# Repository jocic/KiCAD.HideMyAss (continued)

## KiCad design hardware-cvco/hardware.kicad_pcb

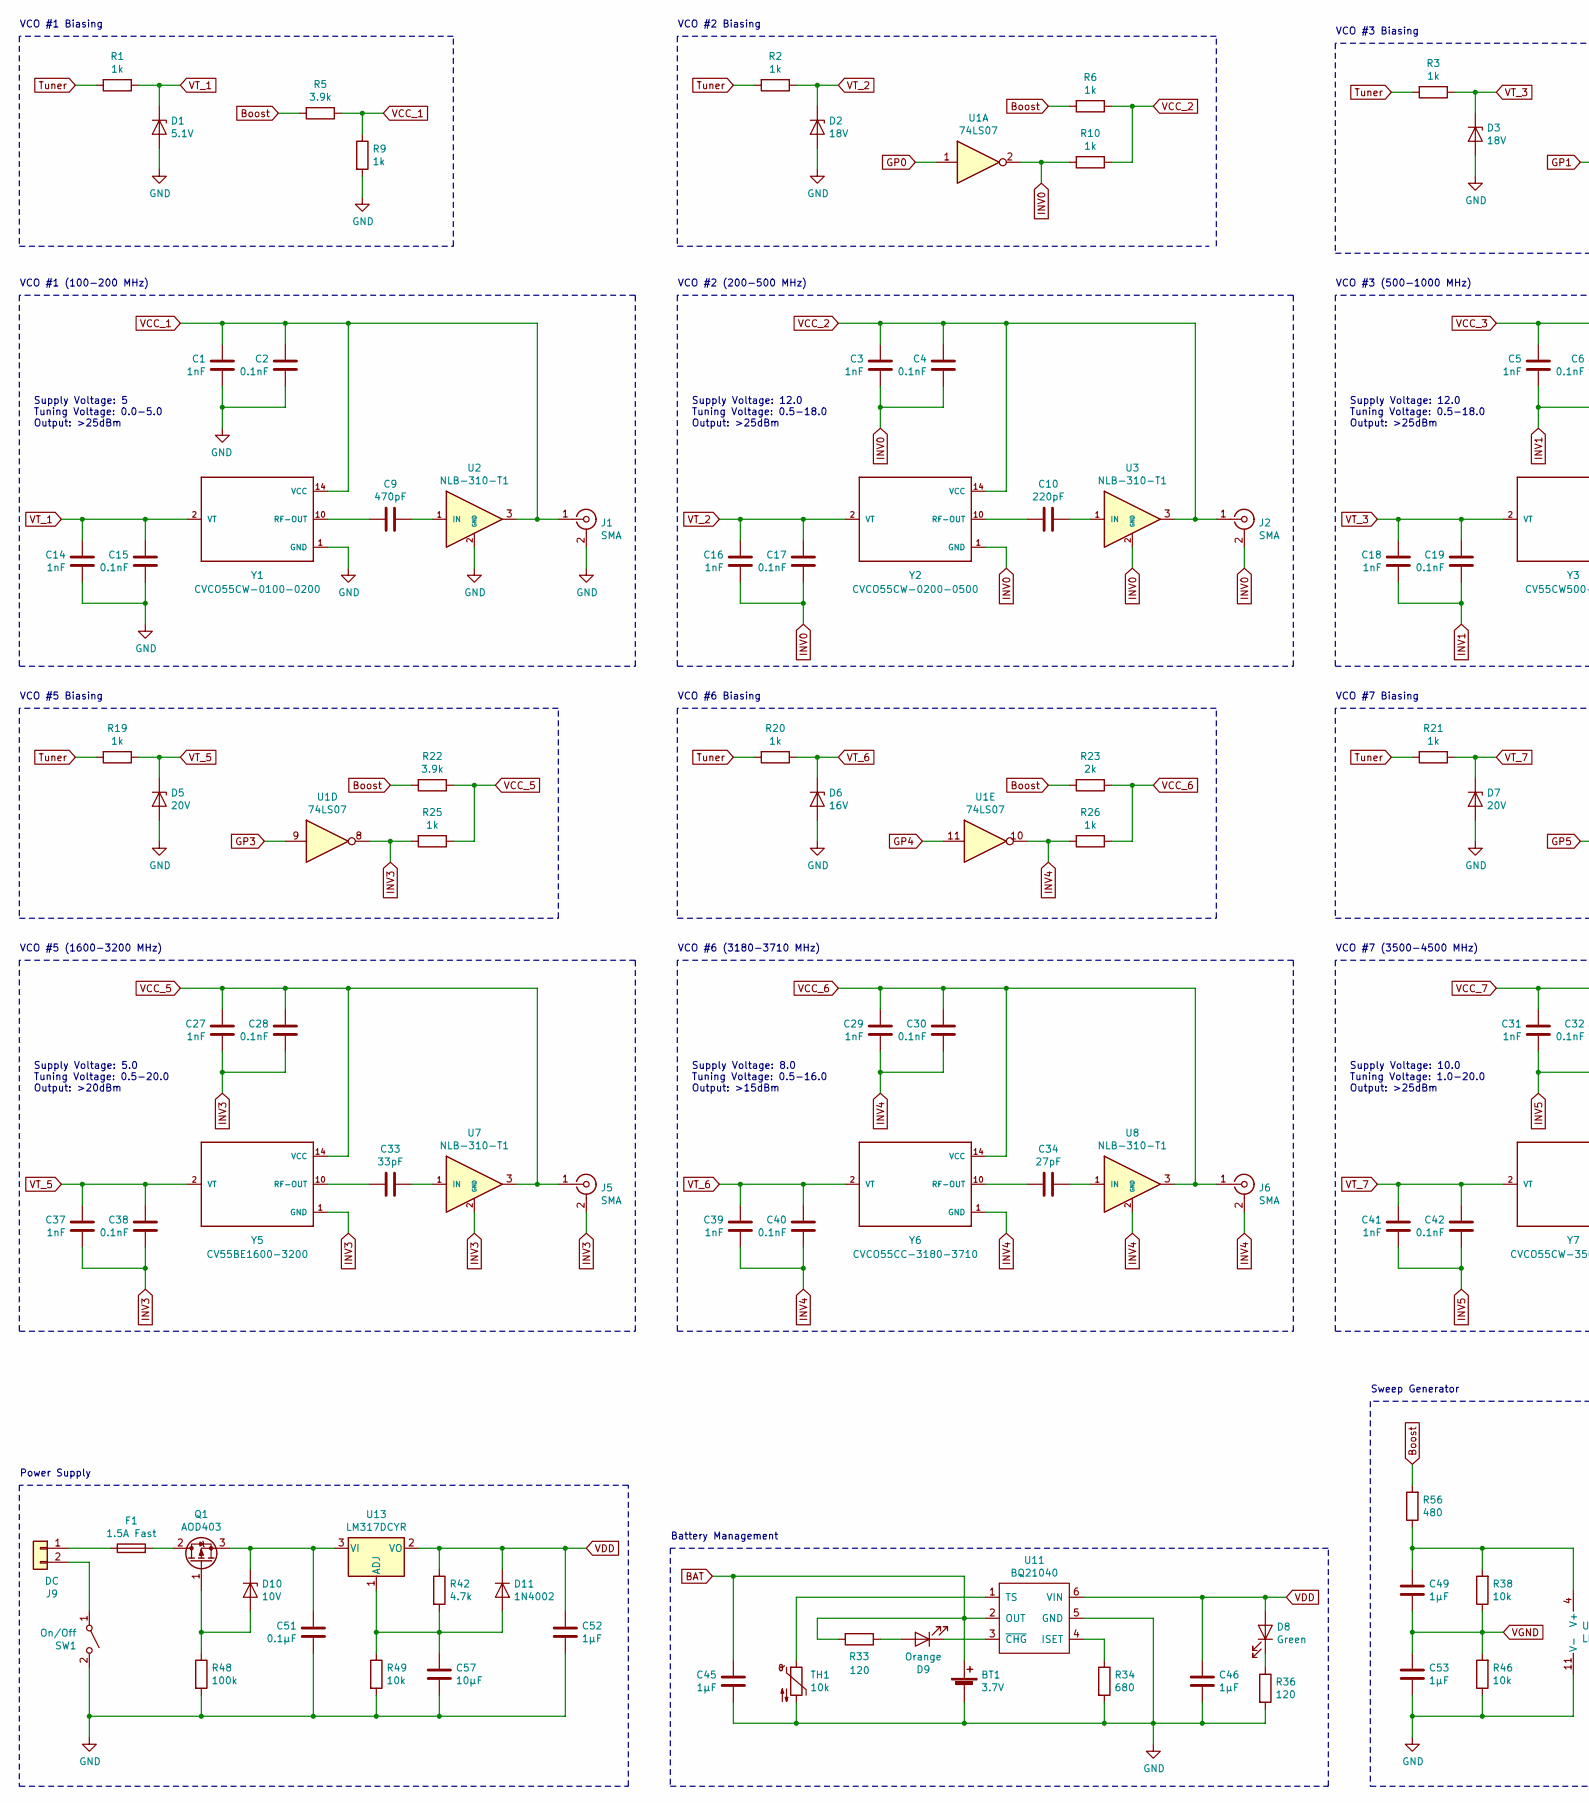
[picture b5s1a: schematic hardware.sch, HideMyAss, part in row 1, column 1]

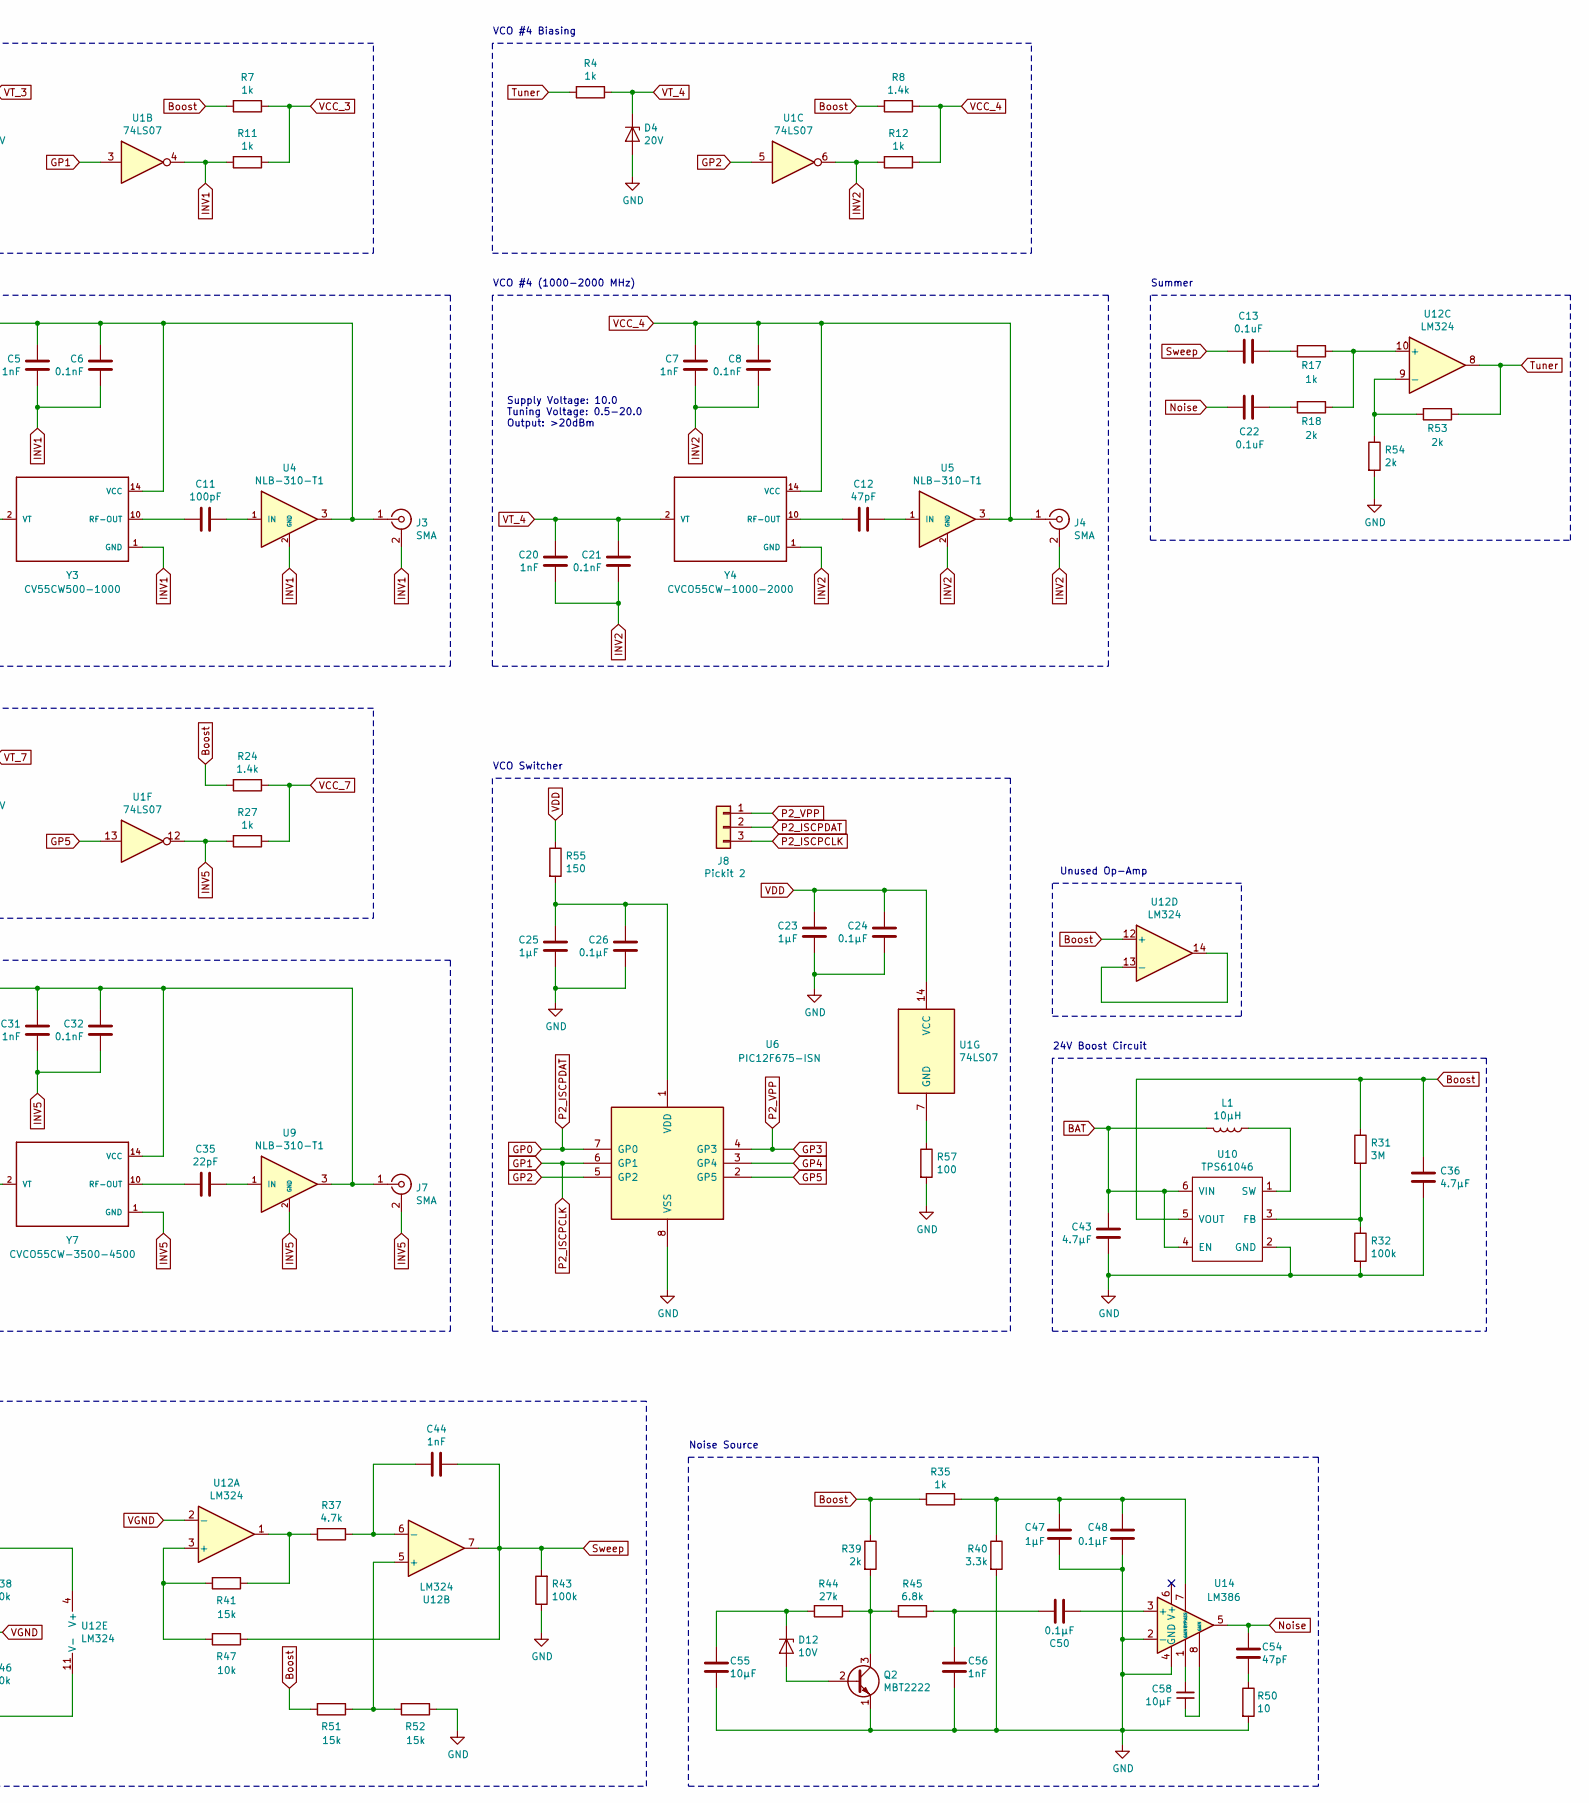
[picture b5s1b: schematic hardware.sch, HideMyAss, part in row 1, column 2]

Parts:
BT1: 3.7V; 2-2.54mm-Horizontal-Molex; LCSC Part # C132504
C1, C3, C5, C7, C14, C16, C18, C20, C27, C29, C31, C37, C39, C41: 1nF; C_0805_2012Metric_Pad1.15x1.40mm_HandSolder; LCSC Part # C1791
C2, C4, C6, C8, C15, C17, C19, C21, C28, C30, C32, C38, C40, C42: 0.1nF; C_0805_2012Metric_Pad1.15x1.40mm_HandSolder; LCSC Part # C159771
C9: 470pF; C_0805_2012Metric_Pad1.15x1.40mm_HandSolder; LCSC Part # C1743
C10: 220pF; C_0805_2012Metric_Pad1.15x1.40mm_HandSolder; LCSC Part # C1727
C11: 100pF; C_0805_2012Metric_Pad1.15x1.40mm_HandSolder; LCSC Part # C1790
C12, C54: 47pF; C_0805_2012Metric_Pad1.15x1.40mm_HandSolder; LCSC Part # C107118
C13, C22: 0.1uF; C_0805_2012Metric_Pad1.15x1.40mm_HandSolder; LCSC Part # C62912
C23, C25, C45, C46, C47, C49, C53: 1μF; C_0805_2012Metric_Pad1.15x1.40mm_HandSolder; LCSC Part # C116352
C24, C26: 0.1μF; C_0805_2012Metric_Pad1.15x1.40mm_HandSolder; LCSC Part # C62912
C33: 33pF; C_0805_2012Metric_Pad1.15x1.40mm_HandSolder; LCSC Part # C157687
C34: 27pF; C_0805_2012Metric_Pad1.15x1.40mm_HandSolder; LCSC Part # C8031
C35: 22pF; C_0805_2012Metric_Pad1.15x1.40mm_HandSolder; LCSC Part # C24658
C36, C43: 4.7μF; C_0805_2012Metric_Pad1.15x1.40mm_HandSolder; LCSC Part # C37818
C44, C56: 1nF; C_0805_2012Metric_Pad1.15x1.40mm_HandSolder
C48, C50: 0.1μF; C_0805_2012Metric_Pad1.15x1.40mm_HandSolder
C51: 0.1μF; C_0805_2012Metric_Pad1.15x1.40mm_HandSolder; LCSC Part # C38141
C52: 1μF; C_0805_2012Metric_Pad1.15x1.40mm_HandSolder; LCSC Part # C215803
C55, C58: 10μF; C_0805_2012Metric_Pad1.15x1.40mm_HandSolder
C57: 10μF; C_0805_2012Metric_Pad1.15x1.40mm_HandSolder; LCSC Part # C40894
D1: 5.1V; D_MiniMELF; LCSC Part # C305343
D2, D3: 18V; D_MiniMELF; LCSC Part # C268731
D4, D5, D7: 20V; D_MiniMELF; LCSC Part # C398899
D6: 16V; D_MiniMELF; LCSC Part # C313481
D8: Green; 2-2.54mm-Horizontal-Molex; LCSC Part # C99763
D9: Orange; 2-2.54mm-Horizontal-Molex; LCSC Part # C99759
D10, D12: 10V; D_MiniMELF; LCSC Part # C398894
D11: 1N4002; D_SMA; LCSC Part # C433393
F1: 1.5A Fast; Fuse_1206_3216Metric_Pad1.42x1.75mm_HandSolder; LCSC Part # C151143
J1, J2, J3, J4, J5, J6, J7: SMA; SMA-Edge; LCSC Part # C530661
J8: Pickit 2; PinSocket_1x03_P2.54mm_Horizontal; LCSC Part # C49257
J9: DC; SolderWirePad_1x02_P3.81mm_Drill1mm
L1: 10μH; C_0805_2012Metric_Pad1.15x1.40mm_HandSolder; LCSC Part # C1046
Q1: AOD403; TO-252-2; LCSC Part # C28969
Q2: MBT2222; SOT-23; LCSC Part # C82460
R1, R6, R7, R9, R10, R11, R12, R17, R25, R26, R27: 1k; R_0805_2012Metric_Pad1.15x1.40mm_HandSolder; LCSC Part # C17513
R2, R3, R4, R19, R20, R21, R35: 1k; R_0805_2012Metric_Pad1.15x1.40mm_HandSolder
R5, R22: 3.9k; R_0805_2012Metric_Pad1.15x1.40mm_HandSolder; LCSC Part # C17614
R8, R24: 1.4k; R_0805_2012Metric_Pad1.15x1.40mm_HandSolder; LCSC Part # C17388
R18, R23, R53, R54: 2k; R_0805_2012Metric_Pad1.15x1.40mm_HandSolder; LCSC Part # C17604
R31: 3M; R_0805_2012Metric_Pad1.15x1.40mm_HandSolder; LCSC Part # C17662
R32, R43: 100k; R_0805_2012Metric_Pad1.15x1.40mm_HandSolder; LCSC Part # C149504
R33, R36: 120; R_0805_2012Metric_Pad1.15x1.40mm_HandSolder; LCSC Part # C111022
R34: 680; R_0805_2012Metric_Pad1.15x1.40mm_HandSolder; LCSC Part # C17798
R37, R42: 4.7k; R_0805_2012Metric_Pad1.15x1.40mm_HandSolder; LCSC Part # C47010
R38, R46, R47, R49: 10k; R_0805_2012Metric_Pad1.15x1.40mm_HandSolder; LCSC Part # C55866
R39: 2k; R_0805_2012Metric_Pad1.15x1.40mm_HandSolder
R40: 3.3k; R_0805_2012Metric_Pad1.15x1.40mm_HandSolder; LCSC Part # C26010
R41, R51, R52: 15k; R_0805_2012Metric_Pad1.15x1.40mm_HandSolder; LCSC Part # C17475
R44: 27k; R_0805_2012Metric_Pad1.15x1.40mm_HandSolder; LCSC Part # C17593
R45: 6.8k; R_0805_2012Metric_Pad1.15x1.40mm_HandSolder; LCSC Part # C17772
R48: 100k; R_0805_2012Metric_Pad1.15x1.40mm_HandSolder; LCSC Part # C55868
R50: 10; R_0805_2012Metric_Pad1.15x1.40mm_HandSolder
R55: 150; R_0805_2012Metric_Pad1.15x1.40mm_HandSolder; LCSC Part # C17513
R56: 480; R_0805_2012Metric_Pad1.15x1.40mm_HandSolder; LCSC Part # C55866
R57: 100; R_0805_2012Metric_Pad1.15x1.40mm_HandSolder; LCSC Part # C17513
SW1: On/Off; 2-2.54mm-Horizontal-Molex; LCSC Part # C505003
TH1: 10k; 2-2.54mm-Horizontal-Molex; LCSC Part # C13879
U1: 74LS07; SOIC-14_3.9x8.7mm_P1.27mm; LCSC Part # C513513
U2, U3, U4, U5, U7, U8, U9: NLB-310-T1; Micro-X-4; Mouser Part # 772-NLB-310
U6: PIC12F675-ISN; SOIC-8_3.9x4.9mm_P1.27mm; LCSC Part # C96100
U10: TPS61046; SOT-23-6_Handsoldering; LCSC Part # C464815
U11: BQ21040; SOT-23-6; LCSC Part # C202311
U12: LM324; SOIC-14_3.9x8.7mm_P1.27mm
U13: LM317DCYR; SOT-223-3_TabPin2; LCSC Part # C51466
U14: LM386; SO-8_5.3x6.2mm_P1.27mm
Y1: CVCO55CW-0100-0200; CVCO55; Mouser Part # 549-CV55CW0100-0200
Y2: CVCO55CW-0200-0500; CVCO55; Mouser Part # 549-CV55CW0200-0500
Y3: CV55CW500-1000; CVCO55; Mouser Part # 549-CV55CW500-1000
Y4: CVCO55CW-1000-2000; CVCO55; Mouser Part # 549-CV55CW1000-2000
Y5: CV55BE1600-3200; CVCO55; Mouser Part # 549-CV55BE1600-3200
Y6: CVCO55CC-3180-3710; CVCO55; Mouser Part # 549-CVCO55CC31803710
Y7: CVCO55CW-3500-4500; CVCO55; Mouser Part # 549-CVC55CW3500-4500

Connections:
BAT: BT1.1 (+), C43.1, C45.1, L1.2, R33.2, U10.4 (EN), U10.6 (VIN), U11.2 (OUT)
Boost: C36.1, R5.2, R6.2, R7.2, R8.2, R22.2, R23.2, R24.2, R31.1, R35.2, R39.1, R51.2, R56.2, U10.5 (VOUT), U12.12 (+)
GND: BT1.2 (-), C1.2, C2.2, C14.2, C15.2, C23.2, C24.2, C25.2, C26.2, C36.2, C43.2, C45.2, C46.2, C47.1, C48.1, C51.2, C52.2, C53.2, C55.1, C56.1, C57.2, D1.2 (A), D2.2 (A), D3.2 (A), D4.2 (A), D5.2 (A), D6.2 (A), D7.2 (A), J1.2 (Ext), Q2.1 (E), R9.2, R32.2, R34.2, R36.2, R40.2, R43.1, R46.1, R48.2, R49.2, R50.2, R52.1, R54.2, R57.2, SW1.2 (B), TH1.2, U2.2 (GND), U2.4 (GND), U6.8 (VSS), U10.2 (GND), U11.5 (GND), U12.11 (V-), U14.2 (-), U14.4 (GND), Y1.1 (GND), Y1.3 (GND), Y1.4 (GND), Y1.5 (GND), Y1.6 (GND), Y1.7 (GND), Y1.8 (GND), Y1.9 (GND), Y1.11 (GND), Y1.12 (GND), Y1.13 (GND), Y1.15 (GND), Y1.16 (GND)
GP0: J8.2, U1.1, U6.7 (GP0)
GP1: J8.3, U1.3, U6.6 (GP1)
GP2: U1.5, U6.5 (GP2)
GP3: J8.1, U1.9, U6.4 (GP3)
GP4: U1.11, U6.3 (GP4)
GP5: U1.13, U6.2 (GP5)
INV0: C3.2, C4.2, C16.2, C17.2, J2.2 (Ext), R10.2, U1.2, U3.2 (GND), U3.4 (GND), Y2.1 (GND), Y2.3 (GND), Y2.4 (GND), Y2.5 (GND), Y2.6 (GND), Y2.7 (GND), Y2.8 (GND), Y2.9 (GND), Y2.11 (GND), Y2.12 (GND), Y2.13 (GND), Y2.15 (GND), Y2.16 (GND)
INV1: C5.2, C6.2, C18.2, C19.2, J3.2 (Ext), R11.2, U1.4, U4.2 (GND), U4.4 (GND), Y3.1 (GND), Y3.3 (GND), Y3.4 (GND), Y3.5 (GND), Y3.6 (GND), Y3.7 (GND), Y3.8 (GND), Y3.9 (GND), Y3.11 (GND), Y3.12 (GND), Y3.13 (GND), Y3.15 (GND), Y3.16 (GND)
INV2: C7.2, C8.2, C20.2, C21.2, J4.2 (Ext), R12.2, U1.6, U5.2 (GND), U5.4 (GND), Y4.1 (GND), Y4.3 (GND), Y4.4 (GND), Y4.5 (GND), Y4.6 (GND), Y4.7 (GND), Y4.8 (GND), Y4.9 (GND), Y4.11 (GND), Y4.12 (GND), Y4.13 (GND), Y4.15 (GND), Y4.16 (GND)
INV3: C27.2, C28.2, C37.2, C38.2, J5.2 (Ext), R25.2, U1.8, U7.2 (GND), U7.4 (GND), Y5.1 (GND), Y5.3 (GND), Y5.4 (GND), Y5.5 (GND), Y5.6 (GND), Y5.7 (GND), Y5.8 (GND), Y5.9 (GND), Y5.11 (GND), Y5.12 (GND), Y5.13 (GND), Y5.15 (GND), Y5.16 (GND)
INV4: C29.2, C30.2, C39.2, C40.2, J6.2 (Ext), R26.2, U1.10, U8.2 (GND), U8.4 (GND), Y6.1 (GND), Y6.3 (GND), Y6.4 (GND), Y6.5 (GND), Y6.6 (GND), Y6.7 (GND), Y6.8 (GND), Y6.9 (GND), Y6.11 (GND), Y6.12 (GND), Y6.13 (GND), Y6.15 (GND), Y6.16 (GND)
INV5: C31.2, C32.2, C41.2, C42.2, J7.2 (Ext), R27.2, U1.12, U9.2 (GND), U9.4 (GND), Y7.1 (GND), Y7.3 (GND), Y7.4 (GND), Y7.5 (GND), Y7.6 (GND), Y7.7 (GND), Y7.8 (GND), Y7.9 (GND), Y7.11 (GND), Y7.12 (GND), Y7.13 (GND), Y7.15 (GND), Y7.16 (GND)
unnamed: C9.1, U2.1 (IN)
unnamed: C9.2, Y1.10 (RF-OUT)
unnamed: C10.1, U3.1 (IN)
unnamed: C10.2, Y2.10 (RF-OUT)
unnamed: C11.1, U4.1 (IN)
unnamed: C11.2, Y3.10 (RF-OUT)
unnamed: C12.1, U5.1 (IN)
unnamed: C12.2, Y4.10 (RF-OUT)
unnamed: C13.1, R17.2
unnamed: C22.1, R18.2
unnamed: C25.1, C26.1, R55.2, U6.1 (VDD)
unnamed: C33.1, U7.1 (IN)
unnamed: C33.2, Y5.10 (RF-OUT)
unnamed: C34.1, U8.1 (IN)
unnamed: C34.2, Y6.10 (RF-OUT)
unnamed: C35.1, U9.1 (IN)
unnamed: C35.2, Y7.10 (RF-OUT)
unnamed: C44.2, R37.1, U12.6 (-)
unnamed: C47.2, C48.2, R35.1, R40.1, U14.7 (BYPASS)
unnamed: C49.1, R38.2, R56.1, U12.4 (V+)
unnamed: C50.1, C56.2, R45.1
unnamed: C50.2, U14.3 (+)
unnamed: C51.1, D10.1 (K), Q1.3 (S), U13.3 (VI)
unnamed: C54.2, R50.1
unnamed: C55.2, D12.1 (K), R44.2
unnamed: C57.1, D11.2 (A), R42.2, R49.1, U13.1 (ADJ)
unnamed: C58.1, U14.8 (GAIN)
unnamed: C58.2, U14.1 (GAIN)
unnamed: D8.1 (K), R36.1
unnamed: D9.1 (K), U11.3 (~CHG~)
unnamed: D9.2 (A), R33.1
unnamed: D10.2 (A), Q1.1 (G), R48.1
unnamed: D12.2 (A), Q2.2 (B)
unnamed: F1.1, J9.1
unnamed: F1.2, Q1.2 (D)
unnamed: J9.2, SW1.1 (A)
unnamed: L1.1, U10.1 (SW)
unnamed: Q2.3 (C), R39.2, R44.1, R45.2
unnamed: R17.1, R18.1, U12.10 (+)
unnamed: R31.2, R32.1, U10.3 (FB)
unnamed: R34.1, U11.4 (ISET)
unnamed: R37.2, R41.1, U12.1
unnamed: R41.2, R47.2, U12.3 (+)
unnamed: R51.1, R52.2, U12.5 (+)
unnamed: R53.2, R54.1, U12.9 (-)
unnamed: R57.1, U1.7 (GND)
unnamed: TH1.1, U11.1 (TS)
unnamed: U12.13 (-), U12.14
Noise: C22.2, C54.1, U14.5
Sweep: C13.2, C44.1, R43.2, R47.1, U12.7
Tuner: R1.2, R2.2, R3.2, R4.2, R19.2, R20.2, R21.2, R53.1, U12.8
VCC_1: C1.1, C2.1, J1.1 (In), R5.1, R9.1, U2.3, Y1.14 (VCC)
VCC_2: C3.1, C4.1, J2.1 (In), R6.1, R10.1, U3.3, Y2.14 (VCC)
VCC_3: C5.1, C6.1, J3.1 (In), R7.1, R11.1, U4.3, Y3.14 (VCC)
VCC_4: C7.1, C8.1, J4.1 (In), R8.1, R12.1, U5.3, Y4.14 (VCC)
VCC_5: C27.1, C28.1, J5.1 (In), R22.1, R25.1, U7.3, Y5.14 (VCC)
VCC_6: C29.1, C30.1, J6.1 (In), R23.1, R26.1, U8.3, Y6.14 (VCC)
VCC_7: C31.1, C32.1, J7.1 (In), R24.1, R27.1, U9.3, Y7.14 (VCC)
VDD: C23.1, C24.1, C46.1, C52.1, D8.2 (A), D11.1 (K), R42.1, R55.1, U1.14 (VCC), U11.6 (VIN), U13.2 (VO)
VGND: C49.2, C53.1, R38.1, R46.2, U12.2 (-)
VT_1: C14.1, C15.1, D1.1 (K), R1.1, Y1.2 (VT)
VT_2: C16.1, C17.1, D2.1 (K), R2.1, Y2.2 (VT)
VT_3: C18.1, C19.1, D3.1 (K), R3.1, Y3.2 (VT)
VT_4: C20.1, C21.1, D4.1 (K), R4.1, Y4.2 (VT)
VT_5: C37.1, C38.1, D5.1 (K), R19.1, Y5.2 (VT)
VT_6: C39.1, C40.1, D6.1 (K), R20.1, Y6.2 (VT)
VT_7: C41.1, C42.1, D7.1 (K), R21.1, Y7.2 (VT)

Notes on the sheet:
Supply Voltage: 12.0 Tuning Voltage: 0.5-18.0 Output: >25dBm
VCO #3 (500-1000 MHz)
Supply Voltage: 10.0 Tuning Voltage: 0.5-20.0 Output: >20dBm
VCO #4 (1000-2000 MHz)
Supply Voltage: 5.0 Tuning Voltage: 0.5-20.0 Output: >20dBm
VCO #5 (1600-3200 MHz)
Supply Voltage: 8.0 Tuning Voltage: 0.5-16.0 Output: >15dBm
VCO #6 (3180-3710 MHz)
Supply Voltage: 5 Tuning Voltage: 0.0-5.0 Output: >25dBm
VCO #1 (100-200 MHz)
VCO #1 Biasing
VCO #2 (200-500 MHz)
Supply Voltage: 10.0 Tuning Voltage: 1.0-20.0 Output: >25dBm
VCO #7 (3500-4500 MHz)
Power Supply
Battery Management
24V Boost Circuit
Sweep Generator
Summer
VCO Switcher
VCO #2 Biasing
VCO #3 Biasing
VCO #4 Biasing
VCO #5 Biasing
VCO #6 Biasing
VCO #7 Biasing
Noise Source
Unused Op-Amp

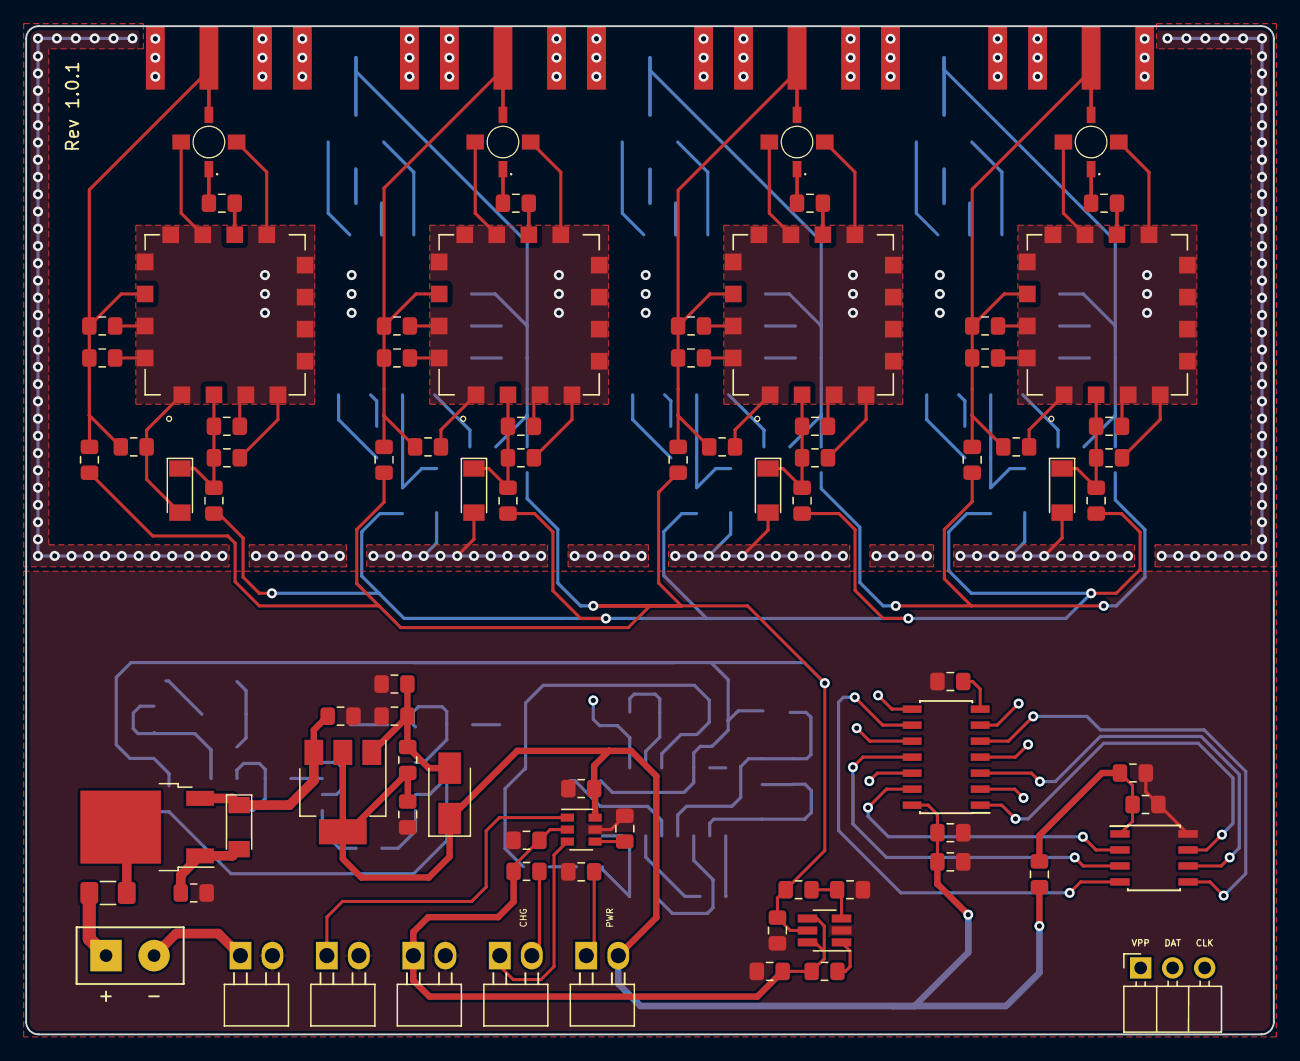
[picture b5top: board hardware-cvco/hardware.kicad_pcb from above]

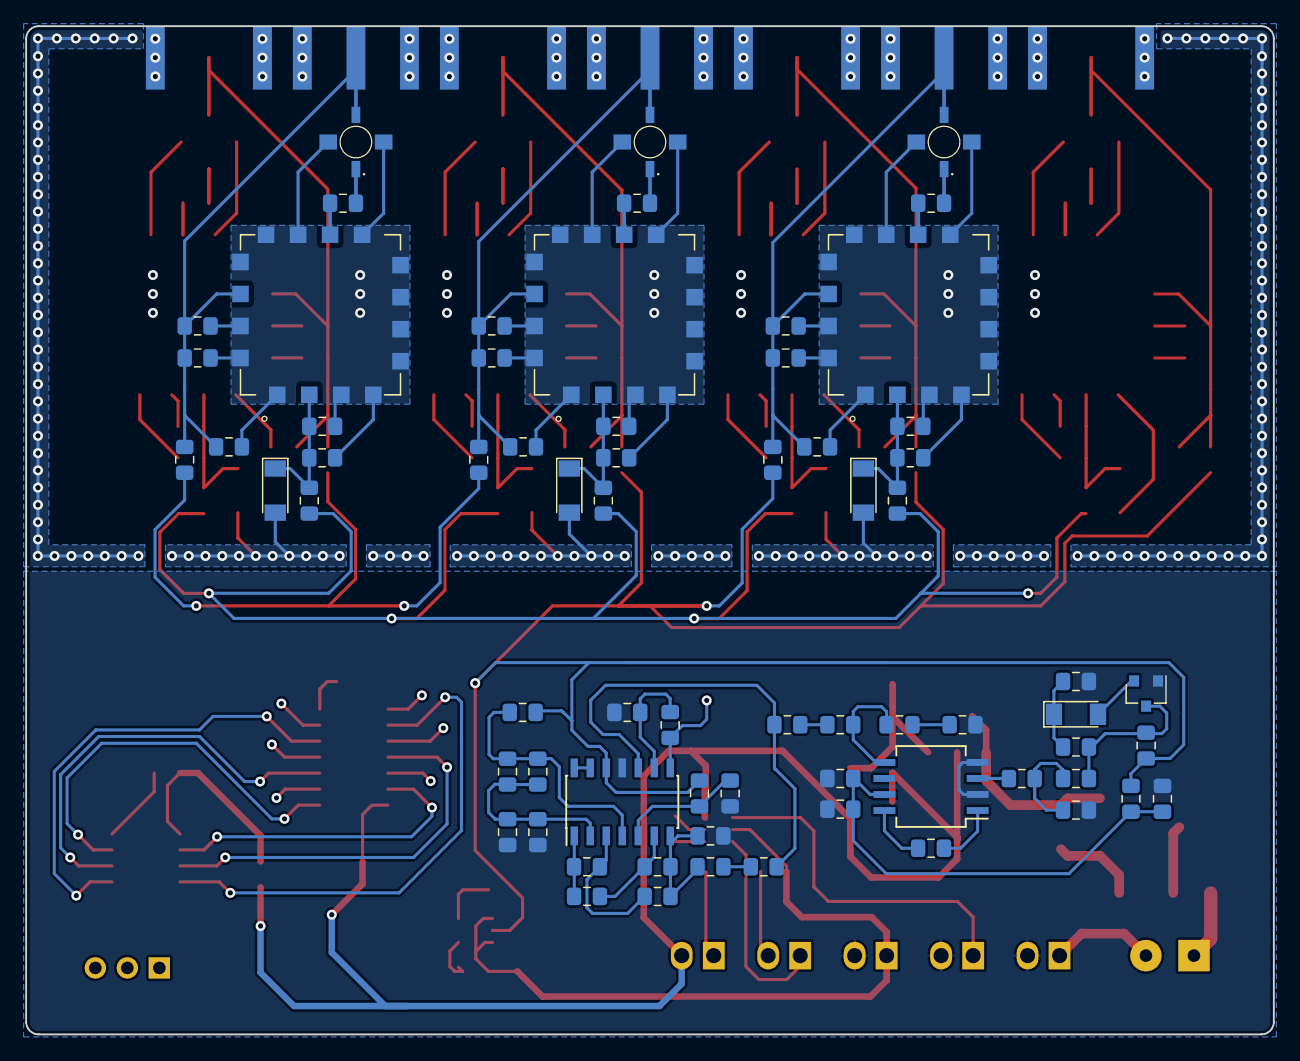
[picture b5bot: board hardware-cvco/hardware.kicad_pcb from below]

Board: 4 copper layers, 99.0 x 80.0 mm, 157 parts (71 on the bottom side), 82 nets.

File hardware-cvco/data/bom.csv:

Reference, Quantity, Value, Footprint, Datasheet, LCSC Part #, Mouser Part #
BT1 ,1,"3.7V","CVCO:2-2.54mm-Horizontal-Molex","~","C132504",""
C1 C3 C5 C7 C27 C29 C31 C14 C16 C18 C20 C41 C39 C37 C44 C56 ,16,"1nF","Capacitor_SMD:C_0805_2012Metric_Pad1.15x1.40mm_HandSolder","~","C1791",""
C10 ,1,"220pF","Capacitor_SMD:C_0805_2012Metric_Pad1.15x1.40mm_HandSolder","~","C1727",""
C11 ,1,"100pF","Capacitor_SMD:C_0805_2012Metric_Pad1.15x1.40mm_HandSolder","~","C1790",""
C12 C54 ,2,"47pF","Capacitor_SMD:C_0805_2012Metric_Pad1.15x1.40mm_HandSolder","~","C107118",""
C13 C22 ,2,"0.1uF","Capacitor_SMD:C_0805_2012Metric_Pad1.15x1.40mm_HandSolder","~","C62912",""
C2 C4 C6 C8 C28 C30 C32 C15 C17 C19 C21 C42 C40 C38 ,14,"0.1nF","Capacitor_SMD:C_0805_2012Metric_Pad1.15x1.40mm_HandSolder","~","C159771",""
C33 ,1,"33pF","Capacitor_SMD:C_0805_2012Metric_Pad1.15x1.40mm_HandSolder","~","C157687",""
C34 ,1,"27pF","Capacitor_SMD:C_0805_2012Metric_Pad1.15x1.40mm_HandSolder","~","C8031",""
C35 ,1,"22pF","Capacitor_SMD:C_0805_2012Metric_Pad1.15x1.40mm_HandSolder","~","C24658",""
C43 C36 ,2,"4.7μF","Capacitor_SMD:C_0805_2012Metric_Pad1.15x1.40mm_HandSolder","~","C37818",""
C51 C24 C50 C48 C26 ,5,"0.1μF","Capacitor_SMD:C_0805_2012Metric_Pad1.15x1.40mm_HandSolder","~","C38141",""
C52 C53 C49 C23 C47 C46 C45 C25 ,8,"1μF","Capacitor_SMD:C_0805_2012Metric_Pad1.15x1.40mm_HandSolder","~","C215803",""
C57 C58 C55 ,3,"10μF","Capacitor_SMD:C_0805_2012Metric_Pad1.15x1.40mm_HandSolder","~","C40894",""
C9 ,1,"470pF","Capacitor_SMD:C_0805_2012Metric_Pad1.15x1.40mm_HandSolder","~","C1743",""
D1 ,1,"5.1V","Diode_SMD:D_MiniMELF","~","C305343",""
D10 D12 ,2,"10V","Diode_SMD:D_MiniMELF","~","C398894",""
D11 ,1,"1N4002","Diode_SMD:D_SMA_Handsoldering","~","C433393",""
D3 D2 ,2,"18V","Diode_SMD:D_MiniMELF","~","C268731",""
D6 ,1,"16V","Diode_SMD:D_MiniMELF","~","C313481",""
D7 D5 D4 ,3,"20V","Diode_SMD:D_MiniMELF","~","C398899",""
D8 ,1,"Green","CVCO:2-2.54mm-Horizontal-Molex","~","C99763",""
D9 ,1,"Orange","CVCO:2-2.54mm-Horizontal-Molex","~","C99759",""
F1 ,1,"1.5A Fast","Fuse:Fuse_1206_3216Metric_Pad1.42x1.75mm_HandSolder","~","C151143",""
J3 J4 J5 J6 J1 J2 J7 ,7,"SMA","CVCO:SMA-Edge"," ~","C530661",""
J8 ,1,"Pickit 2","Connector_PinSocket_2.54mm:PinSocket_1x03_P2.54mm_Horizontal","~","C49257",""
J9 ,1,"DC","Connector_Wire:SolderWirePad_1x02_P3.81mm_Drill1mm","~"
L1 ,1,"10μH","Capacitor_SMD:C_0805_2012Metric_Pad1.15x1.40mm_HandSolder","~","C1046",""
Q1 ,1,"AOD403","Package_TO_SOT_SMD:TO-252-2","https://datasheet.lcsc.com/szlcsc/1811071514_Alpha-Omega-Sem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","C28969",""
Q2 ,1,"MBT2222","Package_TO_SOT_SMD:SOT-23","https://datasheet.lcsc.com/szlcsc/1809272022_ON-Semiconducto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","C82460",""
R1 R17 R35 R9 R6 R21 R20 R19 R4 R7 R3 R2 R10 R11 R12 R25 R26 R27 ,18,"1k","Resistor_SMD:R_0805_2012Metric_Pad1.15x1.40mm_HandSolder","~","C17513",""
R13 R28 ,2,"220","Resistor_SMD:R_0805_2012Metric_Pad1.15x1.40mm_HandSolder","","C17557",""
R14 ,1,"560","Resistor_SMD:R_0805_2012Metric_Pad1.15x1.40mm_HandSolder","","C28636",""
R16 R30 ,2,"470","Resistor_SMD:R_0805_2012Metric_Pad1.15x1.40mm_HandSolder","","C17710",""
R18 R39 R23 R54 R53 ,5,"2k","Resistor_SMD:R_0805_2012Metric_Pad1.15x1.40mm_HandSolder","~","C17604",""
R24 R8 ,2,"1.4k","Resistor_SMD:R_0805_2012Metric_Pad1.15x1.40mm_HandSolder","~","C17388",""
R29 ,1,"270","Resistor_SMD:R_0805_2012Metric_Pad1.15x1.40mm_HandSolder","","C17590",""
R31 ,1,"3M","Resistor_SMD:R_0805_2012Metric_Pad1.15x1.40mm_HandSolder","~","C17662",""
R34 R15 ,2,"680","Resistor_SMD:R_0805_2012Metric_Pad1.15x1.40mm_HandSolder","~","C17798",""
R36 R33 ,2,"120","Resistor_SMD:R_0805_2012Metric_Pad1.15x1.40mm_HandSolder","~","C111022",""
R40 ,1,"3.3k","Resistor_SMD:R_0805_2012Metric_Pad1.15x1.40mm_HandSolder","~","C26010",""
R41 R51 R52 ,3,"15k","Resistor_SMD:R_0805_2012Metric_Pad1.15x1.40mm_HandSolder","~","C17475",""
R42 R37 ,2,"4.7k","Resistor_SMD:R_0805_2012Metric_Pad1.15x1.40mm_HandSolder","~","C47010",""
R44 ,1,"27k","Resistor_SMD:R_0805_2012Metric_Pad1.15x1.40mm_HandSolder","~","C17593",""
R45 ,1,"6.8k","Resistor_SMD:R_0805_2012Metric_Pad1.15x1.40mm_HandSolder","~","C17772",""
R48 R32 R43 ,3,"100k","Resistor_SMD:R_0805_2012Metric_Pad1.15x1.40mm_HandSolder","~","C55868",""
R49 R46 R38 R47 ,4,"10k","Resistor_SMD:R_0805_2012Metric_Pad1.15x1.40mm_HandSolder","~","C55866",""
R5 R22 ,2,"3.9k","Resistor_SMD:R_0805_2012Metric_Pad1.15x1.40mm_HandSolder","~","C17614",""
R50 ,1,"10","Resistor_SMD:R_0805_2012Metric_Pad1.15x1.40mm_HandSolder","~"
R55 ,1,"150","Resistor_SMD:R_0805_2012Metric_Pad1.15x1.40mm_HandSolder","~","C17513",""
R56 ,1,"480","Resistor_SMD:R_0805_2012Metric_Pad1.15x1.40mm_HandSolder","~","C55866",""
R57 ,1,"100","Resistor_SMD:R_0805_2012Metric_Pad1.15x1.40mm_HandSolder","~","C17513",""
SW1 ,1,"On/Off","CVCO:2-2.54mm-Horizontal-Molex","","C505003",""
TH1 ,1,"10k","CVCO:2-2.54mm-Horizontal-Molex","~","C13879",""
U1 ,1,"74LS07","Package_SO:SOIC-14_3.9x8.7mm_P1.27mm","http://www.ti.com/lit/gpn/sn74LS06","C513513",""
U10 ,1,"TPS61046","Package_TO_SOT_SMD:SOT-23-6_Handsoldering","https://datasheet.lcsc.com/szlcsc/2001152032_Texas-Instrumen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","C464815",""
U11 ,1,"BQ21040","Package_TO_SOT_SMD:SOT-23-6","https://datasheet.lcsc.com/szlcsc/1810101925_Texas-Instrumen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","C202311",""
U12 ,1,"LM324","Package_SO:SOIC-14_3.9x8.7mm_P1.27mm","http://www.ti.com/lit/ds/symlink/lm2902-n.pdf","C71035",""
U13 ,1,"LM317DCYR","Package_TO_SOT_SMD:SOT-223-3_TabPin2","https://datasheet.lcsc.com/szlcsc/1811032110_Texas-Instrumen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","C51466",""
U14 ,1,"LM386","Package_SO:SO-8_5.3x6.2mm_P1.27mm","http://www.ti.com/lit/ds/symlink/lm386.pdf"
U4 U5 U7 U8 U2 U3 U9 ,7,"NLB-310-T1","CVCO:Micro-X-4","","","772-NLB-310"
U6 ,1,"PIC12F675-ISN","Package_SO:SOIC-8_3.9x4.9mm_P1.27mm","http://ww1.microchip.com/downloads/en/DeviceDoc/41190G.pdf","C96100",""
Y1 ,1,"CVCO55CW-0100-0200","CVCO:CVCO55","https://www.crystek.com/microwave/admin/webapps/welcome/file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","","549-CV55CW0100-0200"
Y2 ,1,"CVCO55CW-0200-0500","CVCO:CVCO55","https://www.crystek.com/microwave/admin/webapps/welcome/file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","","549-CV55CW0200-0500"
Y3 ,1,"CV55CW500-1000","CVCO:CVCO55","https://www.crystek.com/microwave/admin/webapps/welcome/file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","","549-CV55CW500-1000"
Y4 ,1,"CVCO55CW-1000-2000","CVCO:CVCO55","https://www.crystek.com/microwave/admin/webapps/welcome/file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","","549-CV55CW1000-2000"
Y5 ,1,"CV55BE1600-3200","CVCO:CVCO55","https://www.crystek.com/microwave/admin/webapps/welcome/file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","","549-CV55BE1600-3200"
Y6 ,1,"CVCO55CC-3180-3710","CVCO:CVCO55","https://www.crystek.com/microwave/admin/webapps/welcome/file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","","549-CVCO55CC31803710"
Y7 ,1,"CVCO55CW-3500-4500","CVCO:CVCO55","https://www.crystek.com/microwave/admin/webapps/welcome/file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","","549-CVC55CW3500-4500"

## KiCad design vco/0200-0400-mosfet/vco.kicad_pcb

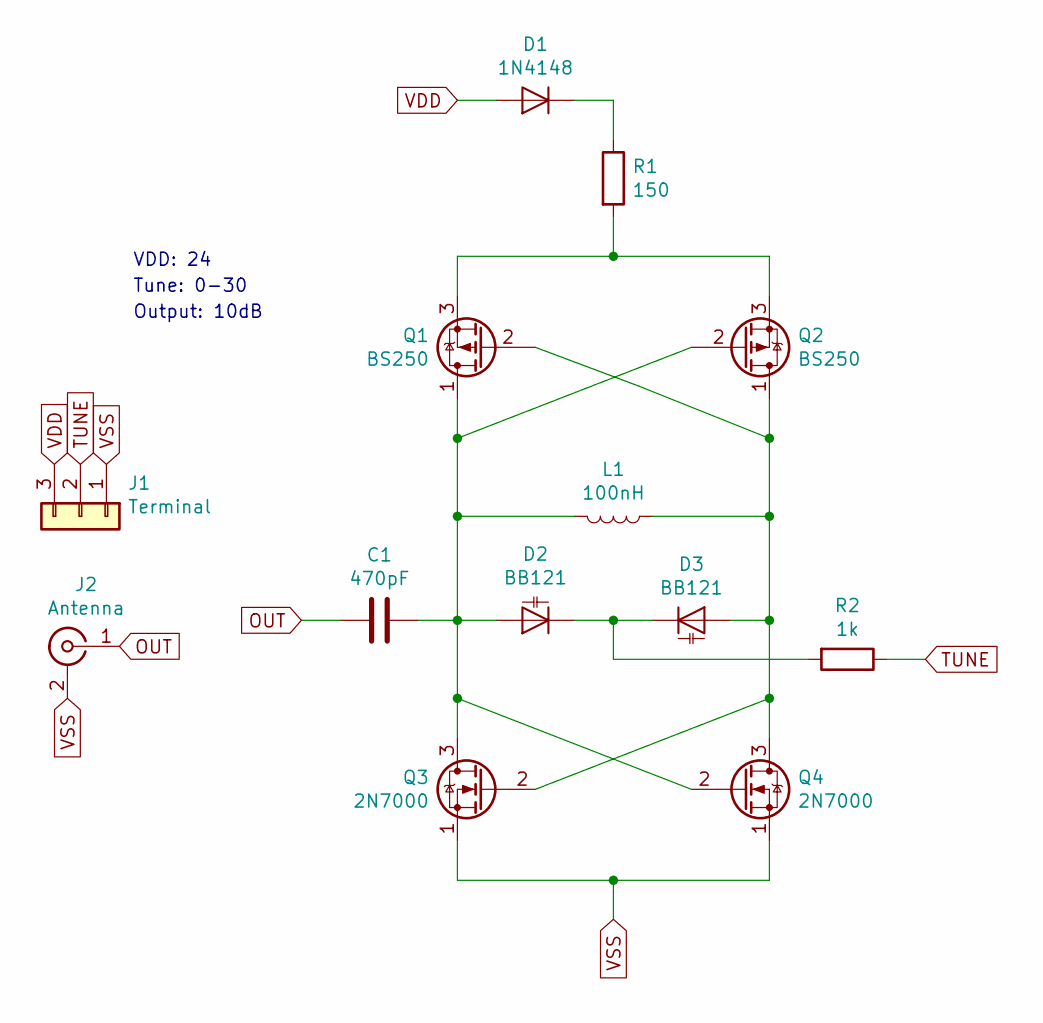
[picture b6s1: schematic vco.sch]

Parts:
C1: 470pF; C_Disc_D5.0mm_W2.5mm_P5.00mm
D1: 1N4148; D_DO-35_SOD27_P7.62mm_Horizontal
D2, D3: BB121; D_DO-35_SOD27_P2.54mm_Vertical_AnodeUp
J1: Terminal; TerminalBlock_4Ucon_1x03_P3.50mm_Horizontal
J2: Antenna; SMA_Amphenol_901-144_Vertical
L1: 100nH; L_Axial_L6.6mm_D2.7mm_P10.16mm_Horizontal_Vishay_IM-2
Q1, Q2: BS250; TO-92L_Wide
Q3, Q4: 2N7000; TO-92L_Wide
R1: 150; R_Axial_Power_L25.0mm_W9.0mm_P27.94mm
R2: 1k; R_Axial_DIN0516_L15.5mm_D5.0mm_P20.32mm_Horizontal

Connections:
unnamed: C1.1, D2.2 (A), L1.2, Q1.1 (D), Q2.2 (G), Q3.3 (D), Q4.2 (G)
unnamed: D1.1 (K), R1.1
unnamed: D2.1 (K), D3.1 (K), R2.2
unnamed: D3.2 (A), L1.1, Q1.2 (G), Q2.1 (D), Q3.2 (G), Q4.3 (D)
unnamed: Q1.3 (S), Q2.3 (S), R1.2
OUT: C1.2, J2.1 (In)
TUNE: J1.2, R2.1
VDD: D1.2 (A), J1.3
VSS: J1.1, J2.2 (Ext), Q3.1 (S), Q4.1 (S)

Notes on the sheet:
VDD: 24
Tune: 0-30
Output: 10dB

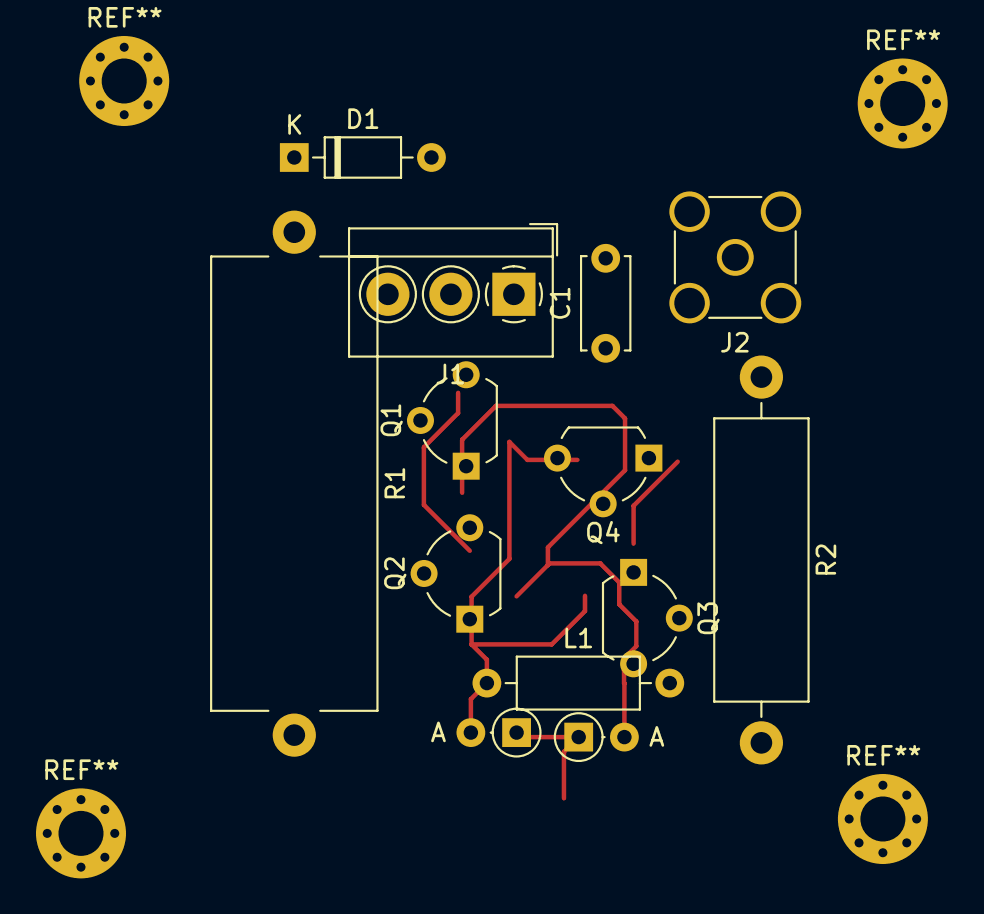
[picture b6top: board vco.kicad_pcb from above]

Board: 2 copper layers, 13 parts (0 on the bottom side), 9 nets.
